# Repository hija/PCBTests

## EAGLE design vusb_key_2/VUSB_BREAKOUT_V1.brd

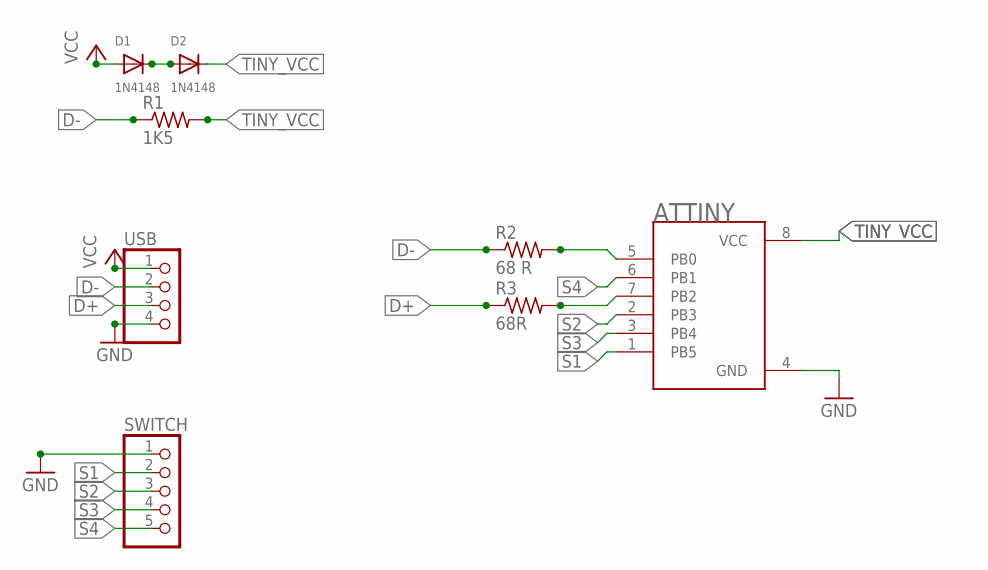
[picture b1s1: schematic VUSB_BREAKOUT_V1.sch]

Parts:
ATTINY: ATTINY85-20PU; DIP762W46P254L927H533Q8B
D1, D2: 1N4148; DO-1N4148
R1: 1K5; 0207/15
R2: 68 R; 0207/15
R3: 68R; 0207/15
SWITCH: PINHD-1X5; 1X05
USB: PINHD-1X4; 1X04

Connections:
D+: R3.1, USB.3
D-: R1.1, R2.1, USB.2
GND: ATTINY.4 (GND), SWITCH.1, USB.4
unnamed: ATTINY.5 (PB0), R2.2
unnamed: D1.C, D2.A
unnamed: ATTINY.7 (PB2), R3.2
S1: ATTINY.1 (PB5), SWITCH.2
S2: ATTINY.2 (PB3), SWITCH.3
S3: ATTINY.3 (PB4), SWITCH.4
S4: ATTINY.6 (PB1), SWITCH.5
TINY_VCC: ATTINY.8 (VCC), D2.C, R1.2
VCC: D1.A, USB.1

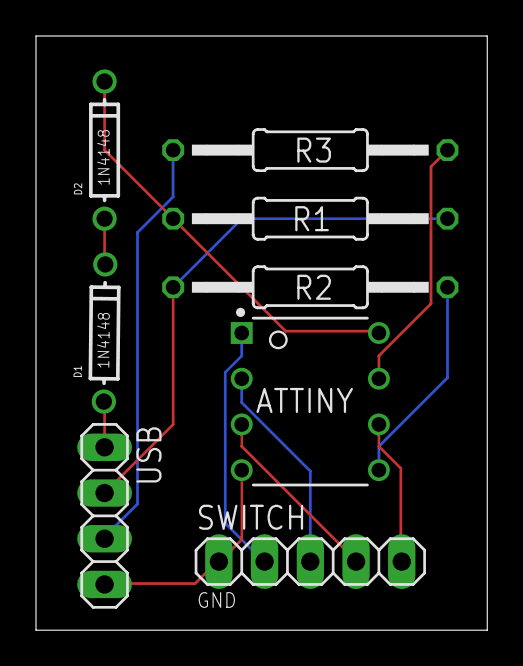
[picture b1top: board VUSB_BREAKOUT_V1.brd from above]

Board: 2 copper layers, 25.1 x 33.0 mm, 8 parts (0 on the bottom side), 12 nets.

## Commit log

2018-03-31 VUSB Breakout Board for attiny
